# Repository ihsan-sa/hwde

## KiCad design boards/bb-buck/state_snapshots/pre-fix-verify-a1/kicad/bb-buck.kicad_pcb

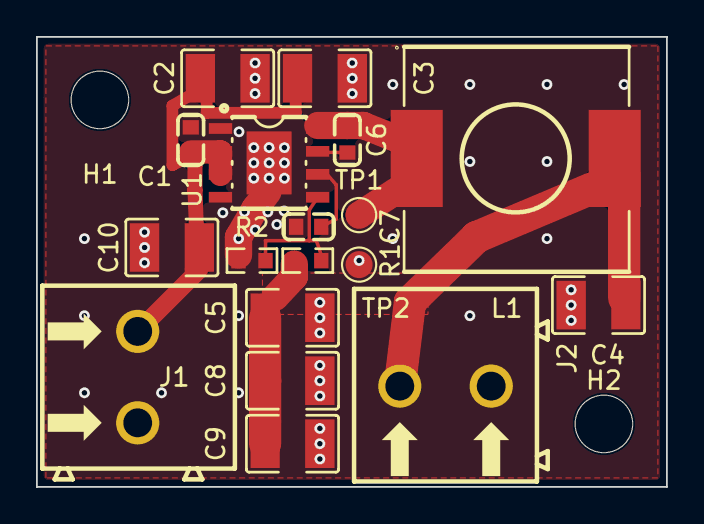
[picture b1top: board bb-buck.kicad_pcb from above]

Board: 2 copper layers, 35.0 x 25.0 mm, 20 parts (0 on the bottom side), 7 nets.

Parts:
C1: 220nF 50V X7R; C0603
C2, C3, C10: 10uF 50V X7R; C1210
C4, C5, C8, C9: 22uF 25V X7R; C1210
C6: 100nF 50V X7R; C0603
C7: 1uF 25V X7R; C0603
H1, H2: M3_3.2mm; MountingHole_3.2mm_M3
J1, J2: KF128-5.08-2P; CONN-TH_P5.08_KF128-5.08-2P
L1: 15uH; IND-SMD_L12.5-W12.5_RLF12545T
R1: 102k 0.1% 25ppm; R0603
R2: 25.5k 0.1% 25ppm; R0603
TP1: SW; TestPoint_Pad_D1.5mm
TP2: GND; TestPoint_Pad_D1.5mm
U1: LMR33630ADDAR; ESOP-8_L4.9-W3.9-P1.27-LS6.0-TL-EP

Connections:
+5V: C4.1, C5.1, C8.1, C9.1, J2.1, L1.2, R1.1
+VIN: C1.1, C2.1, C3.1, C10.1, J1.1, U1.2, U1.3
/BST: C6.1, U1.7
/FB: R1.2, R2.1, U1.5
/SW: C6.2, L1.1, TP1.1, U1.8
/VCC: C7.1, U1.6
GND: C1.2, C2.2, C3.2, C4.2, C5.2, C7.2, C8.2, C9.2, C10.2, J1.2, J2.2, R2.2, TP2.1, U1.1, U1.9

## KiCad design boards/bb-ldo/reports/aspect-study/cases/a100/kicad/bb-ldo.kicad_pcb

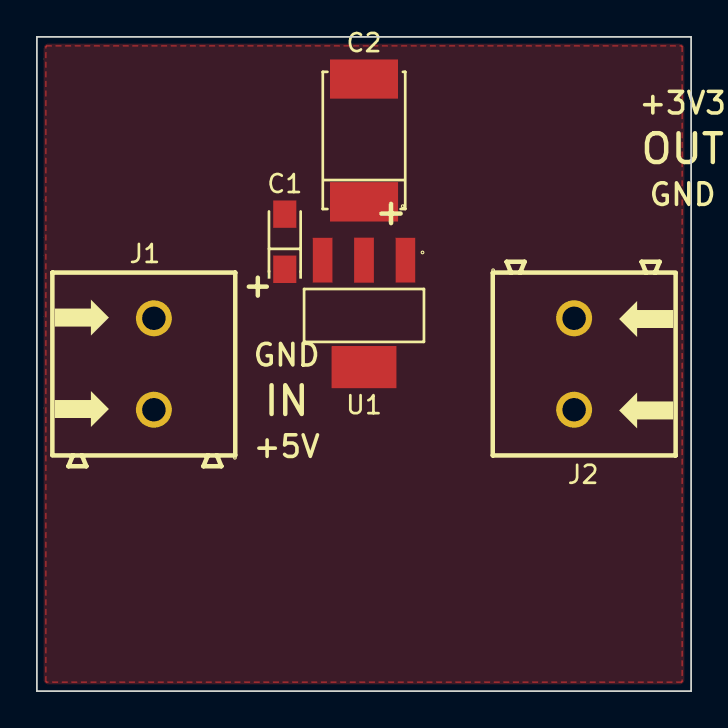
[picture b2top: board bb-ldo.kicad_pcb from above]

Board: 2 copper layers, 36.3 x 36.3 mm, 5 parts (0 on the bottom side), 3 nets, no tracks yet.

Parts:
C1: 10uF 16V solid tantalum; CAP-SMD_L3.2-W1.6-RD-C7171
C2: 22uF 16V solid tantalum ESR 0.8ohm; CAP-SMD_L7.3-W4.3
J1, J2: 2P 5.08mm THT screw terminal; CONN-TH_2P-P5.00_WJ500V-5.08-2P
U1: AMS1117-3.3; SOT-223-3_L6.5-W3.4-P2.30-LS7.0-BR

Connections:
+3V3: C2.1, J2.1, U1.2, U1.4
+5V: C1.1, J1.1, U1.3
GND: C1.2, C2.2, J1.2, J2.2, U1.1
